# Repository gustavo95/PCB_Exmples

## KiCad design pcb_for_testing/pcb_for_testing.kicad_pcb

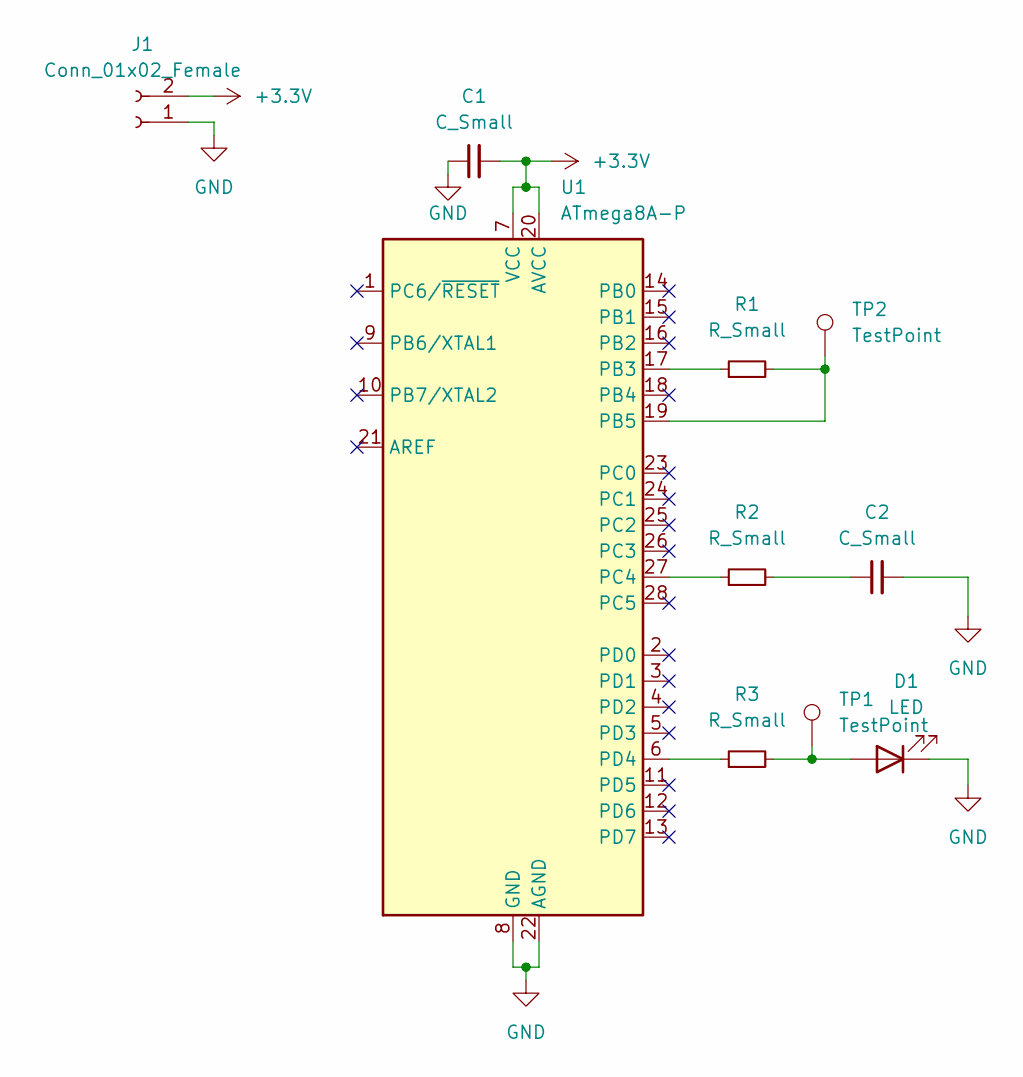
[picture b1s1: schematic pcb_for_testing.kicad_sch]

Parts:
C1, C2: C_Small; C_0805_2012Metric
D1: LED; LED_0805_2012Metric
J1: Conn_01x02_Female; PinHeader_1x02_P1.00mm_Vertical
R1, R2, R3: R_Small; R_0805_2012Metric
TP1, TP2: TestPoint; TestPoint_Pad_D1.0mm
U1: ATmega8A-P; DIP-28_W7.62mm

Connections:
+3V3: C1.2, J1.2, U1.7 (VCC), U1.20 (AVCC)
GND: C1.1, C2.2, D1.1 (K), J1.1, U1.8 (GND), U1.22 (AGND)
unnamed: C2.1, R2.2
unnamed: D1.2 (A), R3.2, TP1.1
unnamed: R1.1, U1.17 (PB3)
unnamed: R1.2, TP2.1, U1.19 (PB5)
unnamed: R2.1, U1.27 (PC4)
unnamed: R3.1, U1.6 (PD4)

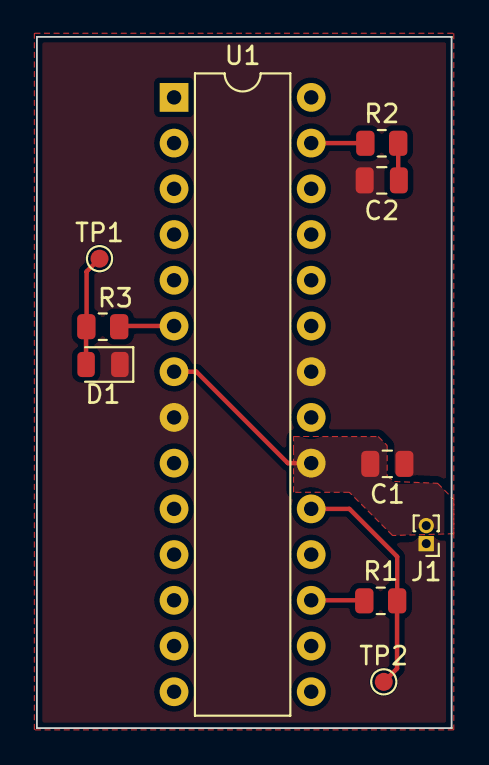
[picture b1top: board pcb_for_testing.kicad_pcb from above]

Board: 2 copper layers, 23.0 x 38.4 mm, 10 parts (0 on the bottom side), 8 nets.

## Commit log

2022-07-04 Creating repository
